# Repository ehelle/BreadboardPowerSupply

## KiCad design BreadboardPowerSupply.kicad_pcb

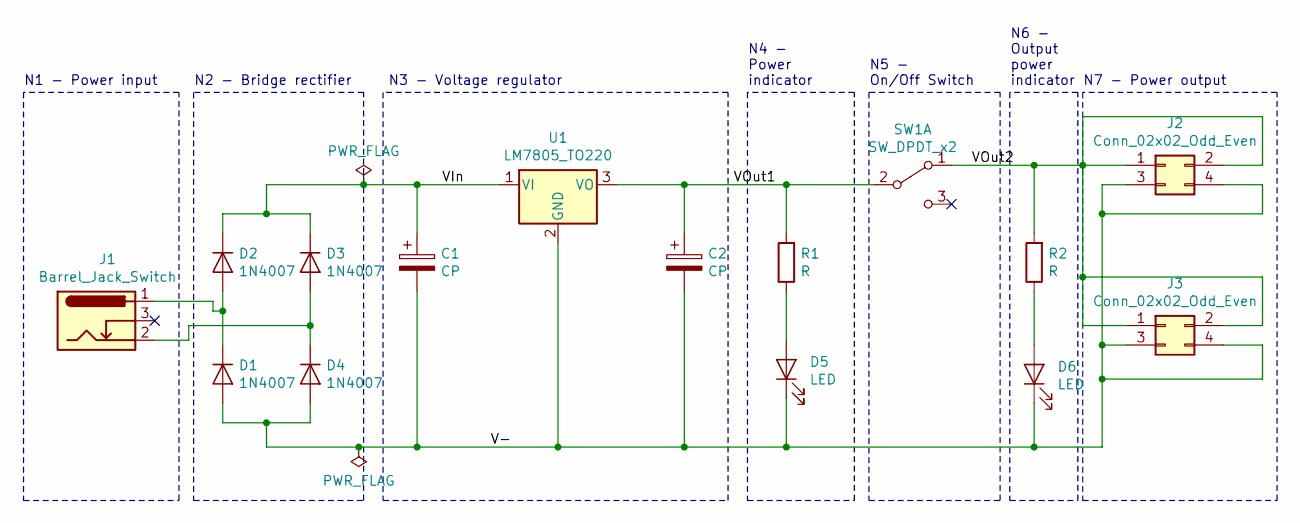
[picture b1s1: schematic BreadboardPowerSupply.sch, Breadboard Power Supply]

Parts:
C1: CP; CP_Radial_D10.0mm_P5.00mm
C2: CP; CP_Radial_D6.3mm_P2.50mm
D1, D2, D3, D4: 1N4007; D_DO-41_SOD81_P10.16mm_Horizontal
D5, D6: LED; LED_D5.0mm
J1: Barrel_Jack_Switch; BarrelJack_CUI_PJ-102AH_Horizontal
J2, J3: Conn_02x02_Odd_Even; PinHeader_2x02_P2.54mm_Vertical
R1, R2: R; R_Axial_DIN0207_L6.3mm_D2.5mm_P7.62mm_Horizontal
SW1: SW_DPDT_x2; Switch_Slide_11.6x4mm_EG1218
U1: LM7805_TO220; TO-220-3_Vertical

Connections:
/V-: C1.2, C2.2, D1.2 (A), D4.2 (A), D5.1 (K), D6.1 (K), J2.3, J2.4, J3.3, J3.4, U1.2 (GND)
/VIn: C1.1, D2.1 (K), D3.1 (K), U1.1 (VI)
/VOut1: C2.1, R1.2, SW1.2 (B), U1.3 (VO)
/VOut2: J2.1, J2.2, J3.1, J3.2, R2.2, SW1.1 (A)
unnamed: D1.1 (K), D2.2 (A), J1.1
unnamed: D3.2 (A), D4.1 (K), J1.2
unnamed: D5.2 (A), R1.1
unnamed: D6.2 (A), R2.1

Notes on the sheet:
N1 - Power input
N2 - Bridge rectifier
N3 - Voltage regulator
N4 - Power indicator
N5 - On/Off Switch
N6 - Output power indicator
N7 - Power output

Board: 2 copper layers, 15 parts (0 on the bottom side), 8 nets, no tracks yet.

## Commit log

2019-12-19 Initial commit - netlist exported
2019-12-19 imported netlist pcbnew
